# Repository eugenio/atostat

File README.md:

# atostat

A modular multichannel potentiostat with bipotentiostat capabilities, designed and built with [atopile](https://atopile.io).

## Key Specifications

- **Current range:** 10 nA to 1 A per channel (8 decades, switched-gain TIA)
- **Voltage range:** +/-2 V (bipolar DAC output via AD5693R + subtractor)
- **Channels:** 2 wired (architecture supports up to 8)
- **Bipotentiostat:** Yes (independent per-channel control)
- **Galvanic isolation:** 5 kV rated per channel (B0505S DC-DC + ISO1640 I2C + ISO7741 SPI/GPIO)
- **Modes:** Potentiostat and galvanostat (analog feedback path switching)
- **Connectivity:** WiFi, USB (ESP32-S3), CAN bus (SN65HVD230)
- **ADC:** Dual per channel -- ADS1256 (fast, 24-bit SPI) + NAU7802 (slow, 24-bit I2C)
- **DAC:** AD5693R (16-bit, I2C) with bipolar output stage
- **Sync:** Hardware trigger input, sync output, shared sync bus for multi-channel triggering

## Architecture Overview

The design is organized into three top-level modules wired together in `main.ato`:

**PowerSupply** -- Generates all voltage rails from a 5-12 V DC input.

- TPS63020 buck-boost converter (5 V analog rail)
- LDK220 LDO (3.3 V digital rail from 5 V)
- TPS60403 charge pump inverter (-5 V rail)

**ConnectivityGateway** -- Central coordinator built around an ESP32-S3.

- TCA9548A I2C multiplexer (8 channel fan-out)
- SPI bus with 74HC138 3-to-8 chip-select demux
- CAN bus transceiver (SN65HVD230) for multi-instrument sync
- External trigger input and sync pulse output

**PotentiostatChannel** (x2 wired) -- Fully isolated analog front end.

- Galvanic isolation: B0505S isolated DC-DC (custom no-Y-cap driver) + ISO1640 I2C isolator + ISO7741 SPI/GPIO isolator
- Control amplifier: AD8608 (quad rail-to-rail op-amp)
- Reference electrode buffer (high-impedance follower)
- Switched-gain TIA: MAX14778 analog mux selecting 8 gain resistor decades
- Mode switch: potentiostat/galvanostat feedback path selection
- Cell disconnect: TS5A22362 analog switch
- ADC interface: ADS1256 (SPI, fast sampling) + NAU7802 (I2C, precision)
- DAC waveform: AD5693R with bipolar subtractor output stage
- Per-channel RP2040 controller (placeholder -- see known issues)

## Module Listing

All custom modules live in `lib/`:

| File | Module | Description |
| ---- | ------ | ----------- |
| `power_supply.ato` | PowerSupply | Multi-rail PSU (5 V, 3.3 V, -5 V) |
| `connectivity.ato` | ConnectivityGateway | ESP32-S3 + I2C mux + SPI CS demux + CAN |
| `channel_module.ato` | PotentiostatChannel | Complete isolated channel assembly |
| `control_amplifier.ato` | ControlAmplifier | AD8608-based control amp with CE drive |
| `re_buffer.ato` | REBuffer | High-impedance reference electrode buffer |
| `switched_gain_tia.ato` | SwitchedGainTIA | 8-decade gain TIA (MAX14778 mux) |
| `adc_interface.ato` | ADCInterface | Dual ADC (ADS1256 + NAU7802) |
| `dac_waveform.ato` | DACWaveform | AD5693R DAC with bipolar output |
| `mode_switch.ato` | ModeSwitch | Potentiostat/galvanostat feedback selector |
| `galvanic_isolator.ato` | GalvanicIsolator | B0505S + ISO1640 I2C isolation |
| `spi_isolator.ato` | SPIIsolator | ISO7741 SPI/GPIO isolation |
| `channel_controller.ato` | ChannelController | Per-channel RP2040 (placeholder) |
| `spi_cs_demux.ato` | SPIChipSelectDemux | 74HC138 3-to-8 CS demux |
| `can_bus.ato` | CANBus | SN65HVD230 CAN transceiver |
| `eis_excitation.ato` | EISExcitation | EIS sine excitation (stub) |
| `ads1256.ato` | ADS1256 | ADS1256 24-bit ADC driver |
| `ad8608.ato` | AD8608 | AD8608 quad op-amp driver |
| `iso7741.ato` | ISO7741 | ISO7741 digital isolator driver |
| `b0505s_no_ycap.ato` | B0505S_NoYcap | B0505S DC-DC without Y-cap (DRC fix) |
| `tps60403.ato` | TPS60403 | TPS60403 charge pump inverter driver |
| `ferrite_bead.ato` | FerriteBead | Murata BLM15AG601SN1D ferrite bead |

## Dependencies

All hardware dependencies are from the atopile registry (see `ato.yaml`):

- `atopile/ti-tps63020` -- Buck-boost converter
- `atopile/st-ldk220` -- LDO regulator
- `atopile/espressif-esp32-s3` -- WiFi/BLE MCU
- `atopile/ti-tca9548a` -- I2C multiplexer
- `atopile/ti-iso1640x` -- Isolated I2C
- `atopile/adi-ad5693r` -- 16-bit DAC
- `atopile/nuvoton-nau7802` -- 24-bit ADC (I2C)
- `atopile/ti-ts5a22362` -- Analog switch
- `atopile/raspberry-rp2040` -- Channel controller MCU
- `ruben-iteng/analog-devices-max14778` -- Analog mux (TIA gain)
- `ruben-iteng/connectors` -- Board connectors
- `ruben-iteng/dcdc-converters` -- Isolated DC-DC

## Building

Requires [atopile](https://atopile.io) >= 0.15.3.

```bash
ato build
```

The build compiles `main.ato:App`, runs all 18 build stages, and picks 189 components. Output goes to `build/`.

## Current Status

**V0.4** -- Two channels fully wired with galvanic isolation, SPI isolation, and CS demux. The build passes cleanly.

### Known Issues

- **RP2040 placeholder:** The per-channel RP2040 controller is a stub. Full integration is blocked by an upstream atopile issue with `has_single_electric_reference_shared` traits in isolated power domains ([atopile/atopile#1812](https://github.com/atopile/atopile/issues/1812)).
- **Tracking issue:** [eugenio/atostat#1](https://github.com/eugenio/atostat/issues/1)

See [docs/V0.4_ROADMAP.md](docs/V0.4_ROADMAP.md) for the full roadmap including resolved and open items.

## License

MIT -- see [LICENSE.txt](LICENSE.txt).

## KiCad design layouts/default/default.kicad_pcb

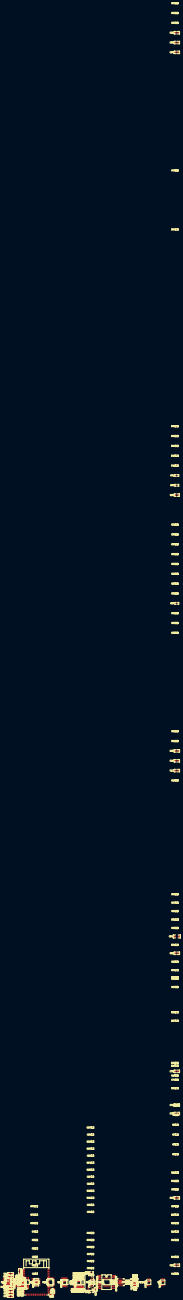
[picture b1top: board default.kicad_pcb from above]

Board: 2 copper layers, 218 parts (0 on the bottom side), 117 nets.

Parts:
C1, C16, C17, C19, C20, C43, C47, C48, C54, C55, C56, C63, C70, C71, C73, C82: 10µF ±10%; C0805
C2, C3, C6, C8, C9, C11, C13, C14, C15, C18, C21, C22, C27, C28, C30, C40, C41, C44, C46, C53, C57, C58, C59, C62, C64, C65, C66, C72, C74, C75, C76, C79, C83, C85, C89, C90, C91, C92, C93, C94, C95, C96, C97, C98, C99: 100nF ±10%; C0402
C4, C5, C45, C60, C61, C68, C69, C86, C87, C88: 1µF ±10%; C0402
C7, C12, C29: 10µF ±20%; C0402
C10, C67: 1nF ±10%; C0402
C23, C31: 10pF ±5%; C0402
C24, C25: 4.7nF ±10%; C0603
C26: 10µF ±10%; C0603
C32, C33: 4pF ±5%; C0402
C34, C35: 47pF ±5%; C0402
C36, C37: 470pF ±10%; C0402
C38, C39: 4.7nF ±10%; C0402
C42: 2.2µF ±20%; C0402
C49, C50, C51, C52: 22µF ±20%; C0805
C77, C78, C80, C81: 100nF ±10%; C0603
C84: 100µF ±20%; C1206
L1, L2: L 4.7µH ±20%; L0603
L3: L 1µH ±20%; IND-SMD_L4.0-W4.0
R1, R11, R12, R13, R16, R25, R26, R27, R28, R29, R30, R33, R34, R35, R36, R47, R48, R49, R50, R51, R52, R53, R54, R55, R56, R57, R58, R59, R60, R61, R62, R63, R65, R66, R72, R73, R80, R81, R82, R83, R84, R85: 10kΩ ±1%; R0402
R2, R3, R4, R5, R6, R7, R8, R9, R15, R38, R64: 1kΩ ±1%; R0402
R10: 10Ω ±1%; R0402
R14: 100kΩ ±1%; R0402
R17, R18, R19, R20: 10kΩ ±0.1%; R0402
R21, R22, R32: L {ℝ+}H; L0402
R23, R70: 15.8kΩ ±1%; R0402
R24, R71: 8.87kΩ ±1%; R0402
R31, R78, R87: 100Ω ±1%; R0402
R37: 10MΩ ±1%; R0603
R39: 100MΩ ±5%; R0805
R40: 20MΩ ±1%; R0603
R41: 2MΩ ±1%; R0603
R42: 200kΩ ±1%; R0402
R43: 20kΩ ±1%; R0402
R44: 2kΩ ±1%; R0402
R45: 200Ω ±1%; R0402
R46: 20Ω ±1%; R0402
R67: 102kΩ ±1%; R0402
R68: 11.3kΩ ±1%; R0402
R69: 1MΩ ±1%; R0402
R74, R75, R76, R77: 49.9Ω ±1%; R0402
R79: 8.06kΩ ±1%; R0402
R86: 120Ω ±1%; R0402
SW1, SW2: KEY-SMD_4P-L4.2-W3.2-P2.20-LS4.6
U1: TSSOP-28_L9.7-W4.4-P0.65-LS6.4-BL
U2: MSOP-10_L3.0-W3.0-P0.50-LS4.9-BL
U3, U11, U14, U16, U22, U23: VSSOP-10_L3.0-W3.0-P0.50-LS4.9-BL
U4: PWRM-TH_B0505S-1WR3
U5: SOIC-16_L10.3-W7.4-P1.27-LS10.3-BL
U6, U12, U15, U19: TSSOP-14_L5.0-W4.4-P0.65-LS6.4-BL
U7: TSSOP-24_L7.8-W4.4-P0.65-LS6.4-BL
U8: WIRELM-SMD_ESP32-S3-WROOM-1
U9: VSON-14_L4.0-W3.0-P0.50-BL-EP_TI_DSJ
U10, U13, U20: SOT-23-5_L3.0-W1.7-P0.95-LS2.8-BL
U17, U18: TQFN-20_L5.0-W5.0-P0.65-TL-EP3.1
U21: SOP-16_L9.9-W3.9-P1.27-LS6.0-BL
U24, U25: SSOP-16_L5.3-W3.4-P0.65-LS5.2
U26: SOIC-8_L4.9-W3.9-P1.27-LS6.0-BL
U27: TSSOP-16_L5.0-W4.4-P0.65-LS6.4-BL

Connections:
2: R2.2, U1.2
3: R3.2, U1.3
4: R4.2, U1.4
8: R38.2, U1.8
16: R82.2, U24.16
DATA_N: U8.13, U26.4
DATA_P: R87.1, U8.14
ENA: R27.1, U17.10
ENB: R28.1, U17.16
PG: R69.1, U9.14
RESET: R72.2, U1.19
RS: R85.1, U26.8
SCL: R11.1, R33.2, R34.2, R48.1, U2.7, U5.6, U5.11, U7.5, U21.13
SDA: R12.1, R35.2, R36.2, R56.1, U2.8, U5.5, U5.12, U7.4, U21.14
SYNC_PDWN: R73.2, U1.18
TXD: U8.11, U26.1
_inductor_1-8: L3.1, U9.8, U9.9
_inductor_2-6: L3.2, U9.6, U9.7
a_inverting: R17.2, R18.2, U12.2
a_inverting_N: R7.1, U14.4, U15.1, U15.2
a_noninverting: R18.1, U6.3, U12.1
bank_switch-enables[1]-7: R26.1, U16.7
c_bw_0-power-hv: C32.1, R39.1, U17.6
c_bw_1-power-hv: C33.1, R40.1, U17.7
c_bw_2-power-hv: C34.1, R41.1, U17.8
c_bw_3-power-hv: C35.1, R42.1, U17.9
c_bw_4-power-hv: C36.1, R43.1, U18.6
c_bw_5-power-hv: C37.1, R44.1, U18.7
c_bw_6-power-hv: C38.1, R45.1, U18.8
c_bw_7-power-hv: C39.1, R46.1, U18.9
c_en-power-hv: C45.1, R66.2, SW2.3, SW2.4, U8.3
can_h: R86.1, U26.7
can_l: R86.2, U26.6
ch0-7: R81.2, U24.7
ch0-7-1: R83.2, U25.7
ch0-16: R84.2, U25.16
ch0-a_noninverting: R19.2, R20.1, U12.3
common_a: U16.2, U18.5
comp_c0-power-hv: C23.1, R78.1, U22.3
comp_c1-power-hv: C66.1, R79.1, U22.9
comp_c2-power-hv: C67.1, R80.1, U23.3
comp_select[0]-line: U22.5, U22.7
current_sense_N: R3.1, R5.2, R75.1
current_sense_P: R2.1, R6.2, R74.1
dac_raw_out: R15.1, U2.10, U11.2
decoupling_capacitor_in[0]-power-hv: C24.1, L1.1, U4.2
decoupling_capacitor_out-power-hv: C26.1, L2.1, U4.4
feedback_divider-ref_out-hv: R23.2, R24.1, U13.4
feedback_divider-ref_out-hv-1: R67.2, R68.1, U9.3
feedback_divider-ref_out-hv-2: R70.2, R71.1, U10.4
feedback_node_P: R8.1, U3.10, U16.3, U19.2
filter_cap-power-lv-1_N: C89.2, R77.2, U21.4
filter_cap-power-lv_N: C6.2, R75.2, U21.2
filter_cap-power-output_P: C89.1, R76.2, U21.5
filter_capacitor-power-hv: C14.1, R15.2, R17.1, U11.3
filter_switch-enables[1]-7: R16.1, U11.7
flying_cap-power-hv: C86.1, U20.5
gpio[11]-line: U3.5, U3.7
gpio[17]-line: R1.2, U1.16
guard_output-b_inverting: U15.6, U15.7
host_in[2]-line: U25.4, U27.15
host_spi-MISO: U8.21, U25.5
host_spi-MOSI: U8.19, U25.3
host_spi-SCLK: U8.20, U25.2
hv: C1.1, C2.1, C7.1, C8.1, C9.1, C11.1, C12.1, C15.1, C16.1, C17.1, C18.1, C20.1, C22.1, C28.1, C29.1, C30.1, C40.1, C62.1, C63.1, C64.1, C65.1, C68.1, C71.1, C72.1, C73.1, C74.1, C75.1, C76.1, C79.1, C82.1, C83.1, C92.1, C93.1, C95.1, C97.1, L2.2, R14.2, R21.2, R27.2, R29.2, R34.1, R36.1, R82.1, R84.1, U1.1, U1.24, U2.1, U3.1, U5.14, U6.4, U11.1, U12.4, U13.1, U13.3, U14.1, U15.4, U16.1, U17.13, U18.13, U19.4, U22.1, U23.1, U24.15, U25.15
i2c_mux-reset-nRESET: R47.1, U7.3
i2cs[1]-SCL: R49.1, U7.7
i2cs[1]-SDA: R57.1, U7.6
i2cs[2]-SCL: R50.1, U7.9
i2cs[2]-SDA: R58.1, U7.8
i2cs[3]-SCL: R51.1, U7.11
i2cs[3]-SDA: R59.1, U7.10
i2cs[4]-SCL: R52.1, U7.14
i2cs[4]-SDA: R60.1, U7.13
i2cs[5]-SCL: R53.1, U7.16
i2cs[5]-SDA: R61.1, U7.15
i2cs[6]-SCL: R54.1, U7.18
i2cs[6]-SDA: R62.1, U7.17
i2cs[7]-SCL: R55.1, U7.20
i2cs[7]-SDA: R63.1, U7.19
input_guard_cap-power-hv: C31.1, R37.2, U15.3, U15.5
io[15]-line: R64.1, U8.8
io[17]-line: R31.1, U8.10
io[21]-line: U8.23, U27.1
io[38]-line: U8.31, U27.2
io[39]-line: U8.32, U27.3
lv: C23.2, C66.2, C67.2, R10.1, R78.2, R79.2, R80.2, U6.1
lv_N: C1.2, C2.2, C3.2, C4.2, C5.2, C7.2, C8.2, C9.2, C10.2, C11.2, C12.2, C13.2, C14.2, C15.2, C16.2, C17.2, C18.2, C20.2, C22.2, C26.2, C28.2, C29.2, C30.2, C31.2, C40.2, C41.2, C42.2, C43.2, C44.2, C45.2, C46.2, C54.2, C57.2, C61.2, C62.2, C63.2, C64.2, C65.2, C68.2, C69.2, C70.2, C71.2, C72.2, C73.2, C74.2, C75.2, C76.2, C77.2, C78.2, C79.2, C80.2, C81.2, C82.2, C83.2, C84.2, C85.2, C90.2, C91.2, C92.2, C93.2, C95.2, C96.2, C97.2, C98.2, C99.2, R5.1, R9.2, R13.2, R16.2, R20.2, R24.2, R25.2, R26.2, R28.2, R30.2, R71.2, R85.2, SW1.1, SW1.2, SW2.1, SW2.2, U1.5, U1.6, U1.7, U1.17, U1.25, U1.27, U2.5, U2.6, U3.6, U4.3, U5.9, U5.16, U6.11, U7.1, U7.2, U7.12, U7.21, U8.1, U8.40, U8.41, U11.6, U12.11, U13.2, U14.6, U15.11, U16.6, U17.3, U18.3, U19.3, U19.11, U21.7, U21.8, U21.9, U22.6, U23.6, U24.14, U25.8, U25.14, U26.2, U27.5, U27.8
lv_P: C32.2, C33.2, C34.2, C35.2, C36.2, C37.2, C38.2, C39.2, R6.1, R39.2, R40.2, R41.2, R42.2, R43.2, R44.2, R45.2, R46.2, U14.2, U19.1
mux_b-enable_a-ENA: R29.1, U18.10
mux_b-enable_b-ENB: R30.1, U18.16
nLDAC: R13.1, U2.4
nRESET: R14.1, U2.3
negative_charge_pump_capacitor-power-hv: C77.1, U17.4, U17.21
negative_charge_pump_capacitor-power-hv-1: C80.1, U18.4, U18.21
output: R65.2, SW1.3, SW1.4, U8.27
output_P: C6.1, R74.2, U21.3
positive_charge_pump_capacitor-power-hv: C78.1, U17.2
positive_charge_pump_capacitor-power-hv-1: C81.1, U18.2
power_5v-hv: C19.1, C21.1, C25.1, C27.1, C49.1, C50.1, C51.1, C52.1, C55.1, C58.1, C60.1, C87.1, C94.1, L1.2, R33.1, R35.1, R67.1, R69.2, R81.1, U5.3, U9.4, U9.5, U10.1, U10.3, U20.1, U24.1
power_in-hv: C47.1, C48.1, U9.10, U9.11
power_in-lv: C47.2, C48.2, U9.2, U9.15
power_in_a_capacitor-power-hv: C53.1, U9.1, U9.12, U9.13
power_neg-hv: C19.2, C21.2, C24.2, C25.2, C27.2, C49.2, C50.2, C51.2, C52.2, C55.2, C56.1, C58.2, C59.1, C60.2, C87.2, C88.1, C94.2, R68.2, U4.1, U5.1, U5.7, U10.2, U20.2, U24.8
power_neg-lv: C56.2, C59.2, C86.2, C88.2, U20.3
sense_inputs[1]_N: R7.2, R38.1, R77.1
sense_inputs[1]_P: R4.1, R8.2, R76.1
snubber_capacitor-power-hv: C10.1, R10.2, U3.2
sw-enables[1]-7: R25.1, U14.7
switches_nc[0]-common_a: U16.4, U17.5
switches_no[0]-2: U6.2, U14.3, U22.2, U22.10, U23.2
touch[8]-SDA: U7.23, U8.12
touch[9]-SCL: U7.22, U8.17
touch[10]-line: U8.18, U27.4
vbg_cap-power-hv: C91.1, U21.6
vref_cap-power-hv: C13.1, R19.1, U2.9
wifi_bypass_cap-power-hv: C3.1, C4.1, C5.1, C41.1, C42.1, C43.1, C44.1, C46.1, C54.1, C57.1, C61.1, C69.1, C70.1, C84.1, C85.1, C90.1, C96.1, C98.1, C99.1, R1.1, R11.2, R12.2, R21.1, R23.1, R32.1, R32.2, R47.2, R48.2, R49.2, R50.2, R51.2, R52.2, R53.2, R54.2, R55.2, R56.2, R57.2, R58.2, R59.2, R60.2, R61.2, R62.2, R63.2, R65.1, R66.1, R70.1, R72.1, R73.1, R83.1, U1.26, U2.2, U7.24, U8.2, U10.5, U13.5, U21.1, U21.15, U21.16, U25.1, U26.3, U27.6, U27.16
